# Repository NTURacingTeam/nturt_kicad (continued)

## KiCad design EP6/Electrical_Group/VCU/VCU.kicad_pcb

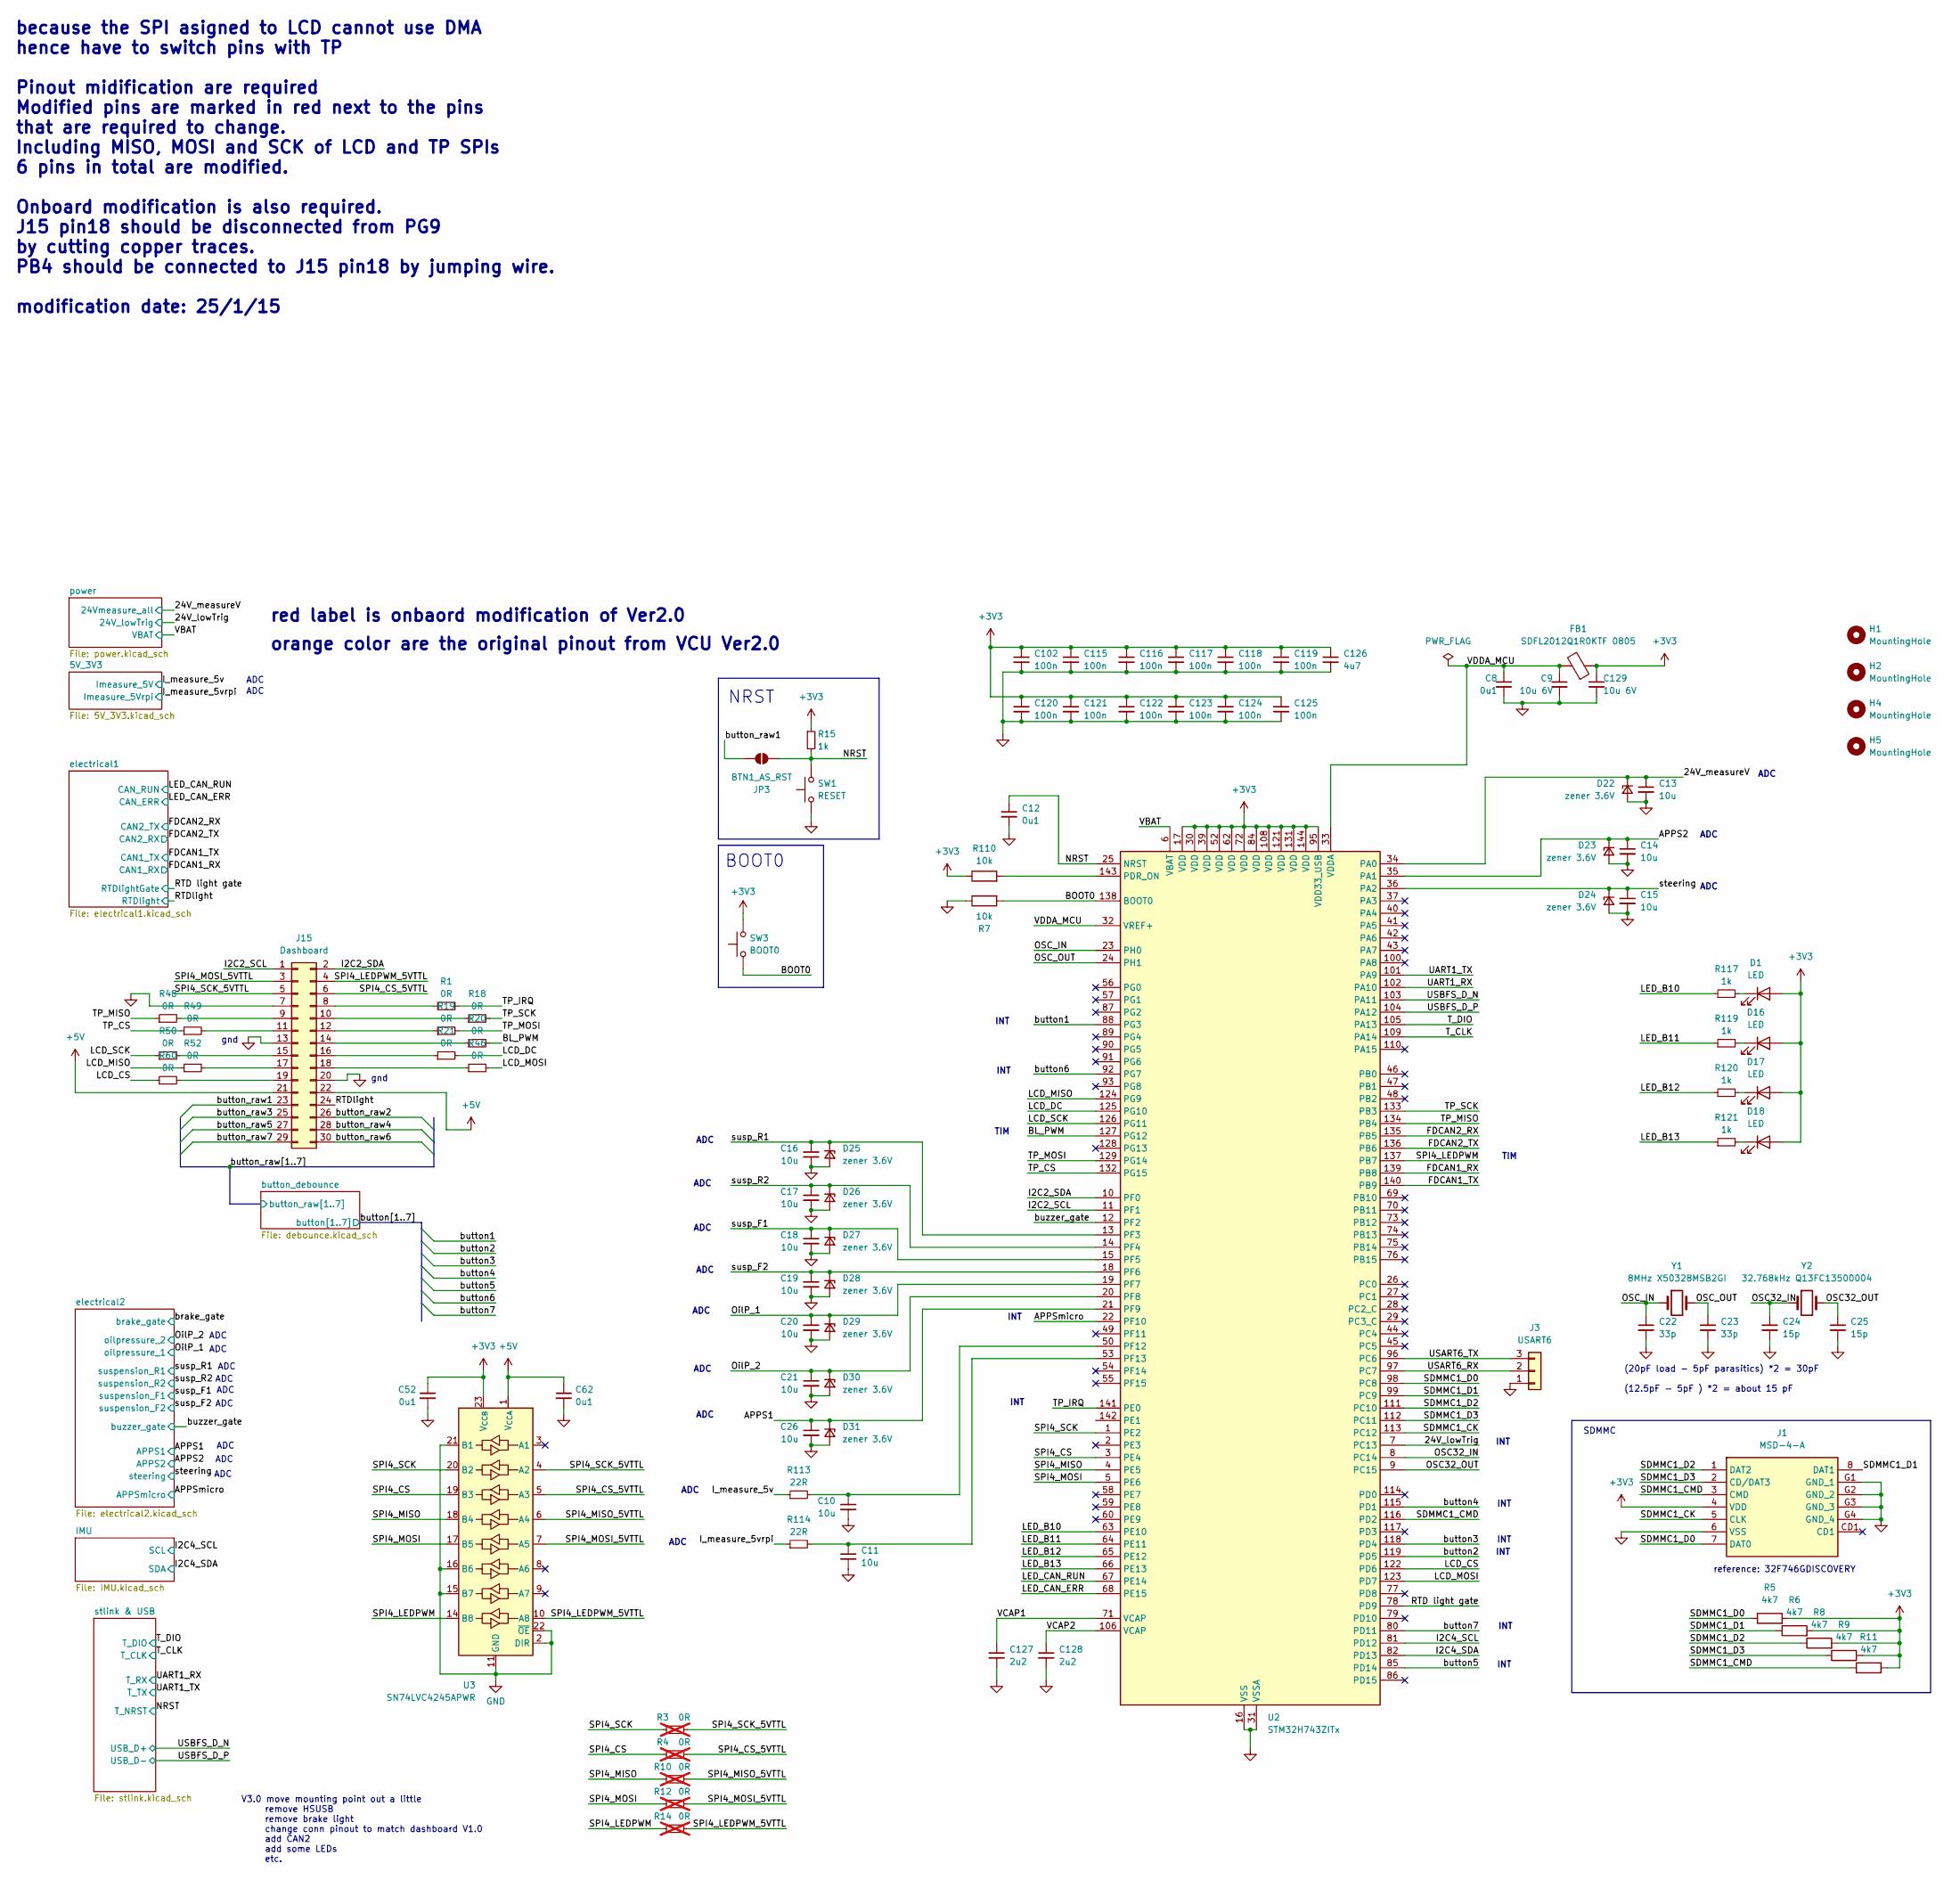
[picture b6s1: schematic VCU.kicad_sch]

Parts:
C8, C12, C52, C62: 0u1; C_0402_1005Metric
C9, C129: 10u 6V; C_0402_1005Metric
C10, C11, C13, C14, C15, C16, C17, C18, C19, C20, C21, C26: 10u; C_0402_1005Metric
C22, C23: 33p; C_0402_1005Metric
C24, C25: 15p; C_0402_1005Metric
C102, C115, C116, C117, C118, C119, C120, C121, C122, C123, C124, C125: 100n; C_0402_1005Metric
C126: 4u7; C_0402_1005Metric
C127, C128: 2u2; C_0402_1005Metric
D1, D16, D17, D18: LED; LED_0603_1608Metric
D22, D23, D24, D25, D26, D27, D28, D29, D30, D31: zener 3.6V; D_SOD-523
FB1: SDFL2012Q1R0KTF 0805; L_0805_2012Metric
H1, H2, H4, H5: MountingHole; MountingHole_3.2mm_M3
J1: MSD-4-A; MSD4A; Mouser Part Number 179-MSD-4-A
J3: USART6; JST_PH_B3B-PH-K_1x03_P2.00mm_Vertical
J15: Dashboard; IDC-Header_2x15_P2.54mm_Vertical
JP3: BTN1_AS_RST; SolderJumper-2_P1.3mm_Open_RoundedPad1.0x1.5mm
R1, R18, R19, R20, R21, R46, R48, R49, R50, R52, R60: 0R; R_0402_1005Metric
R3, R4, R10, R12, R14: 0R; R_0603_1608Metric_Pad0.98x0.95mm_HandSolder; not fitted
R5, R6, R8, R9, R11: 4k7; R_0402_1005Metric
R7, R110: 10k; R_0402_1005Metric
R15, R117, R119, R120, R121: 1k; R_0402_1005Metric
R113, R114: 22R; R_0402_1005Metric
SW1: RESET; SW_Tactile_SPST_NO_Straight_CK_PTS636Sx25SMTRLFS
SW3: BOOT0; SW_Tactile_SPST_NO_Straight_CK_PTS636Sx25SMTRLFS
U2: STM32H743ZITx; LQFP-144_20x20mm_P0.5mm
U3: SN74LVC4245APWR; TSSOP-24_4.4x7.8mm_P0.65mm
Y1: 8MHz X50328MSB2GI; Crystal_SMD_5032-2Pin_5.0x3.2mm
Y2: 32.768kHz Q13FC13500004; Crystal_SMD_3215-2Pin_3.2x1.5mm

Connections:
+3V3: C52.1, C102.1, C115.1, C116.1, C117.1, C118.1, C119.1, C120.1, C121.1, C122.1, C123.1, C124.1, C125.1, C126.1, C129.1, D1.2 (A), D16.2 (A), D17.2 (A), D18.2 (A), FB1.1, J1.4 (VDD), R5.2, R6.2, R8.2, R9.2, R11.2, R15.1, R110.1, SW3.2, U2.17 (VDD), U2.30 (VDD), U2.39 (VDD), U2.52 (VDD), U2.62 (VDD), U2.72 (VDD), U2.84 (VDD), U2.95 (VDD33_USB), U2.108 (VDD), U2.121 (VDD), U2.131 (VDD), U2.144 (VDD), U3.23 (V_{CCB}), U3.24 (V_{CCB}); also elsewhere on the board
+5V: C62.1, J15.21, J15.22, U3.1 (V_{CCA}); also elsewhere on the board
/24V_lowTrig: U2.7 (PC13); also elsewhere on the board
/24V_measureV: C13.1, D22.1 (K), U2.34 (PA0); also elsewhere on the board
/APPS1: C26.1, D31.1 (K), U2.21 (PF9); also elsewhere on the board
/APPS2: C14.1, D23.1 (K), U2.35 (PA1); also elsewhere on the board
/APPSmicro: U2.22 (PF10); also elsewhere on the board
/BL_PWM: R20.2, U2.127 (PG12)
/BOOT0: R7.2, SW3.1, U2.138 (BOOT0)
/FDCAN1_RX: U2.139 (PB8); also elsewhere on the board
/FDCAN1_TX: U2.140 (PB9); also elsewhere on the board
/FDCAN2_RX: U2.135 (PB5); also elsewhere on the board
/FDCAN2_TX: U2.136 (PB6); also elsewhere on the board
/I2C2_SCL: J15.1, U2.11 (PF1)
/I2C2_SDA: J15.2, U2.10 (PF0)
/I2C4_SCL: U2.81 (PD12); also elsewhere on the board
/I2C4_SDA: U2.82 (PD13); also elsewhere on the board
/I_measure_5v: R113.1; also elsewhere on the board
/I_measure_5vrpi: R114.1; also elsewhere on the board
/LCD_CS: R60.1, U2.122 (PD6)
/LCD_DC: R21.2, U2.125 (PG10)
/LCD_MISO: R52.1, U2.124 (PG9)
/LCD_MOSI: R46.2, U2.123 (PD7)
/LCD_SCK: R50.1, U2.126 (PG11)
/LED_B10: R117.1, U2.63 (PE10)
/LED_B11: R119.1, U2.64 (PE11)
/LED_B12: R120.1, U2.65 (PE12)
/LED_B13: R121.1, U2.66 (PE13)
/LED_CAN_ERR: U2.68 (PE15); also elsewhere on the board
/LED_CAN_RUN: U2.67 (PE14); also elsewhere on the board
/NRST: C12.1, JP3.1 (A), R15.2, SW1.2, U2.25 (NRST); also elsewhere on the board
/OSC32_IN: C24.1, U2.8 (PC14), Y2.1
/OSC32_OUT: C25.1, U2.9 (PC15), Y2.2
/OSC_IN: C22.1, U2.23 (PH0), Y1.1
/OSC_OUT: C23.1, U2.24 (PH1), Y1.2
/OilP_1: C20.1, D29.1 (K), U2.19 (PF7); also elsewhere on the board
/OilP_2: C21.1, D30.1 (K), U2.20 (PF8); also elsewhere on the board
/RTD light gate: U2.78 (PD9); also elsewhere on the board
/RTDlight: J15.24; also elsewhere on the board
/SDMMC1_CK: J1.5 (CLK), U2.113 (PC12)
/SDMMC1_CMD: J1.3 (CMD), R11.1, U2.116 (PD2)
/SDMMC1_D0: J1.7 (DAT0), R5.1, U2.98 (PC8)
/SDMMC1_D1: J1.8 (DAT1), R6.1, U2.99 (PC9)
/SDMMC1_D2: J1.1 (DAT2), R8.1, U2.111 (PC10)
/SDMMC1_D3: J1.2 (CD/DAT3), R9.1, U2.112 (PC11)
/SPI4_CS: R4.1, U2.3 (PE4), U3.19 (B3)
/SPI4_CS_5VTTL: J15.6, R4.2, U3.5 (A3)
/SPI4_LEDPWM: R14.1, U2.137 (PB7), U3.14 (B8)
/SPI4_LEDPWM_5VTTL: J15.4, R14.2, U3.10 (A8)
/SPI4_MISO: R10.1, U2.4 (PE5), U3.18 (B4)
/SPI4_MISO_5VTTL: R10.2, U3.6 (A4)
/SPI4_MOSI: R12.1, U2.5 (PE6), U3.17 (B5)
/SPI4_MOSI_5VTTL: J15.3, R12.2, U3.7 (A5)
/SPI4_SCK: R3.1, U2.1 (PE2), U3.20 (B2)
/SPI4_SCK_5VTTL: J15.5, R3.2, U3.4 (A2)
/TP_CS: R49.1, U2.132 (PG15)
/TP_IRQ: R1.1, U2.141 (PE0)
/TP_MISO: R48.1, U2.134 (PB4)
/TP_MOSI: R19.2, U2.129 (PG14)
/TP_SCK: R18.2, U2.133 (PB3)
/T_CLK: U2.109 (PA14); also elsewhere on the board
/T_DIO: U2.105 (PA13); also elsewhere on the board
/UART1_RX: U2.102 (PA10); also elsewhere on the board
/UART1_TX: U2.101 (PA9); also elsewhere on the board
/USART6_RX: J3.2, U2.97 (PC7)
/USART6_TX: J3.3, U2.96 (PC6)
/USBFS_D_N: U2.103 (PA11); also elsewhere on the board
/USBFS_D_P: U2.104 (PA12); also elsewhere on the board
/VBAT: U2.6 (VBAT); also elsewhere on the board
/VCAP1: C127.1, U2.71 (VCAP)
/VCAP2: C128.1, U2.106 (VCAP)
/VDDA_MCU: C8.1, C9.1, FB1.2, U2.32 (VREF+), U2.33 (VDDA)
/button1: U2.88 (PG3); also elsewhere on the board
/button2: U2.119 (PD5); also elsewhere on the board
/button3: U2.118 (PD4); also elsewhere on the board
/button4: U2.115 (PD1); also elsewhere on the board
/button5: U2.85 (PD14); also elsewhere on the board
/button6: U2.92 (PG7); also elsewhere on the board
/button7: U2.80 (PD11); also elsewhere on the board
/button_raw1: J15.23, JP3.2 (B); also elsewhere on the board
/button_raw2: J15.26; also elsewhere on the board
/button_raw3: J15.25; also elsewhere on the board
/button_raw4: J15.28; also elsewhere on the board
/button_raw5: J15.27; also elsewhere on the board
/button_raw6: J15.30; also elsewhere on the board
/button_raw7: J15.29; also elsewhere on the board
/buzzer_gate: U2.12 (PF2); also elsewhere on the board
/steering: C15.1, D24.1 (K), U2.36 (PA2); also elsewhere on the board
/susp_F1: C18.1, D27.1 (K), U2.15 (PF5); also elsewhere on the board
/susp_F2: C19.1, D28.1 (K), U2.18 (PF6); also elsewhere on the board
/susp_R1: C16.1, D25.1 (K), U2.13 (PF3); also elsewhere on the board
/susp_R2: C17.1, D26.1 (K), U2.14 (PF4); also elsewhere on the board
GND: C8.2, C9.2, C10.2, C11.2, C12.2, C13.2, C14.2, C15.2, C16.2, C17.2, C18.2, C19.2, C20.2, C21.2, C22.2, C23.2, C24.2, C25.2, C26.2, C52.2, C62.2, C102.2, C115.2, C116.2, C117.2, C118.2, C119.2, C120.2, C121.2, C122.2, C123.2, C124.2, C125.2, C126.2, C127.2, C128.2, C129.2, D22.2 (A), D23.2 (A), D24.2 (A), D25.2 (A), D26.2 (A), D27.2 (A), D28.2 (A), D29.2 (A), D30.2 (A), D31.2 (A), J1.6 (VSS), J1.G1 (GND_1), J1.G2 (GND_2), J1.G3 (GND_3), J1.G4 (GND_4), J3.1, J15.7, J15.13, J15.20, R7.1, SW1.1, U2.16 (VSS), U2.31 (VSSA), U2.38 (VSS), U2.51 (VSS), U2.61 (VSS), U2.83 (VSS), U2.94 (VSS), U2.107 (VSS), U2.120 (VSS), U2.130 (VSS), U3.2 (DIR), U3.11 (GND), U3.12 (GND), U3.13 (GND), U3.15 (B7), U3.16 (B6), U3.21 (B1), U3.22 (~OE); also elsewhere on the board
unnamed: D1.1 (K), R117.2
unnamed: D16.1 (K), R119.2
unnamed: D17.1 (K), R120.2
unnamed: D18.1 (K), R121.2
unnamed: J15.8, R1.2
unnamed: J15.9, R48.2
unnamed: J15.10, R18.1
unnamed: J15.11, R49.2
unnamed: J15.12, R19.1
unnamed: J15.14, R20.1
unnamed: J15.15, R50.2
unnamed: J15.16, R21.1
unnamed: J15.17, R52.2
unnamed: J15.18, R46.1
unnamed: J15.19, R60.2
unnamed: R110.2, U2.143 (PDR_ON)
unnamed: C10.1, R113.2, U2.50 (PF12)
unnamed: C11.1, R114.2, U2.53 (PF13)

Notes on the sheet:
INT
ADC
BOOT0
NRST
gnd
orange color are the original pinout from VCU Ver2.0
V3.0 move mounting point out a little remove HSUSB remove brake light change conn pinout to match dashboard V1.0 add CAN2 add some LEDs etc.
TIM
SDMMC
reference: 32F746GDISCOVERY
(20pF load - 5pF parasitics) *2 = 30pF (12.5pF - 5pF ) *2 = about 15 pF
red label is onbaord modification of Ver2.0
because the SPI asigned to LCD cannot use DMA hence have to switch pins with TP Pinout midification are required Modified pins are marked in red next to the pins that are required to change. Including MISO, MOSI and SCK of LCD and TP SPIs 6 pins in total are modified. Onboard modification is also r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

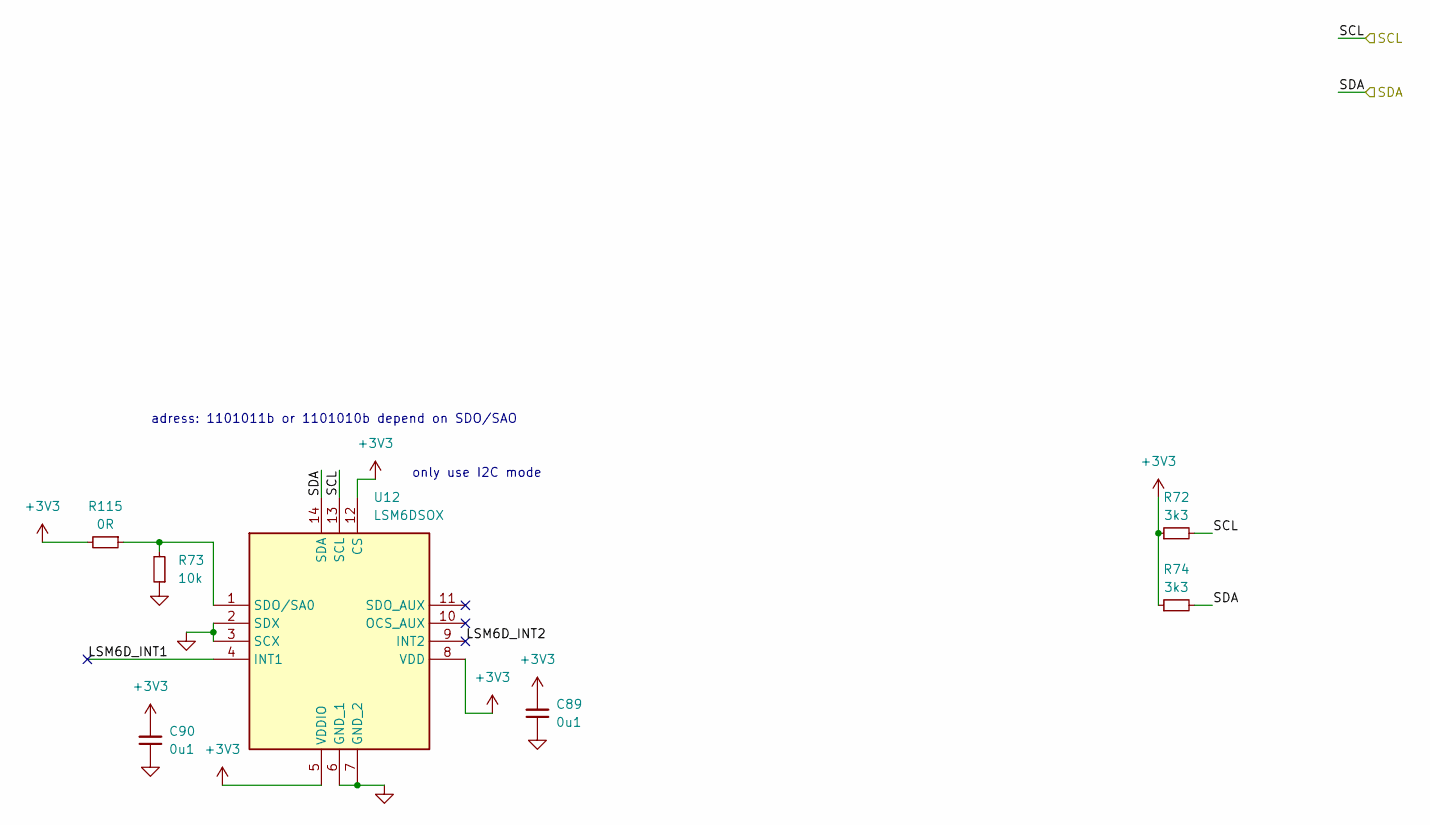
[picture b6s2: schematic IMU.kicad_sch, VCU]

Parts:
C89, C90: 0u1; C_0402_1005Metric
R72, R74: 3k3; R_0402_1005Metric
R73: 10k; R_0402_1005Metric
R115: 0R; R_0402_1005Metric
U12: LSM6DSOX; LGA-14_3x2.5mm_P0.5mm_LayoutBorder3x4y; Mouser Part Number 511-LSM6DSOXTR

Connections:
+3V3: C89.2, C90.2, R72.1, R74.1, R115.2, U12.5 (VDDIO), U12.8 (VDD), U12.12 (CS); also elsewhere on the board
/I2C4_SCL: R72.2, U12.13 (SCL); also elsewhere on the board
/I2C4_SDA: R74.2, U12.14 (SDA); also elsewhere on the board
/IMU/LSM6D_INT1: U12.4 (INT1)
/IMU/LSM6D_INT2: U12.9 (INT2)
GND: C89.1, C90.1, R73.1, U12.2 (SDX), U12.3 (SCX), U12.6 (GND_1), U12.7 (GND_2); also elsewhere on the board
unnamed: R73.2, R115.1, U12.1 (SDO/SA0)

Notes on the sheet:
adress: 1101011b or 1101010b depend on SDO/SAO
only use I2C mode

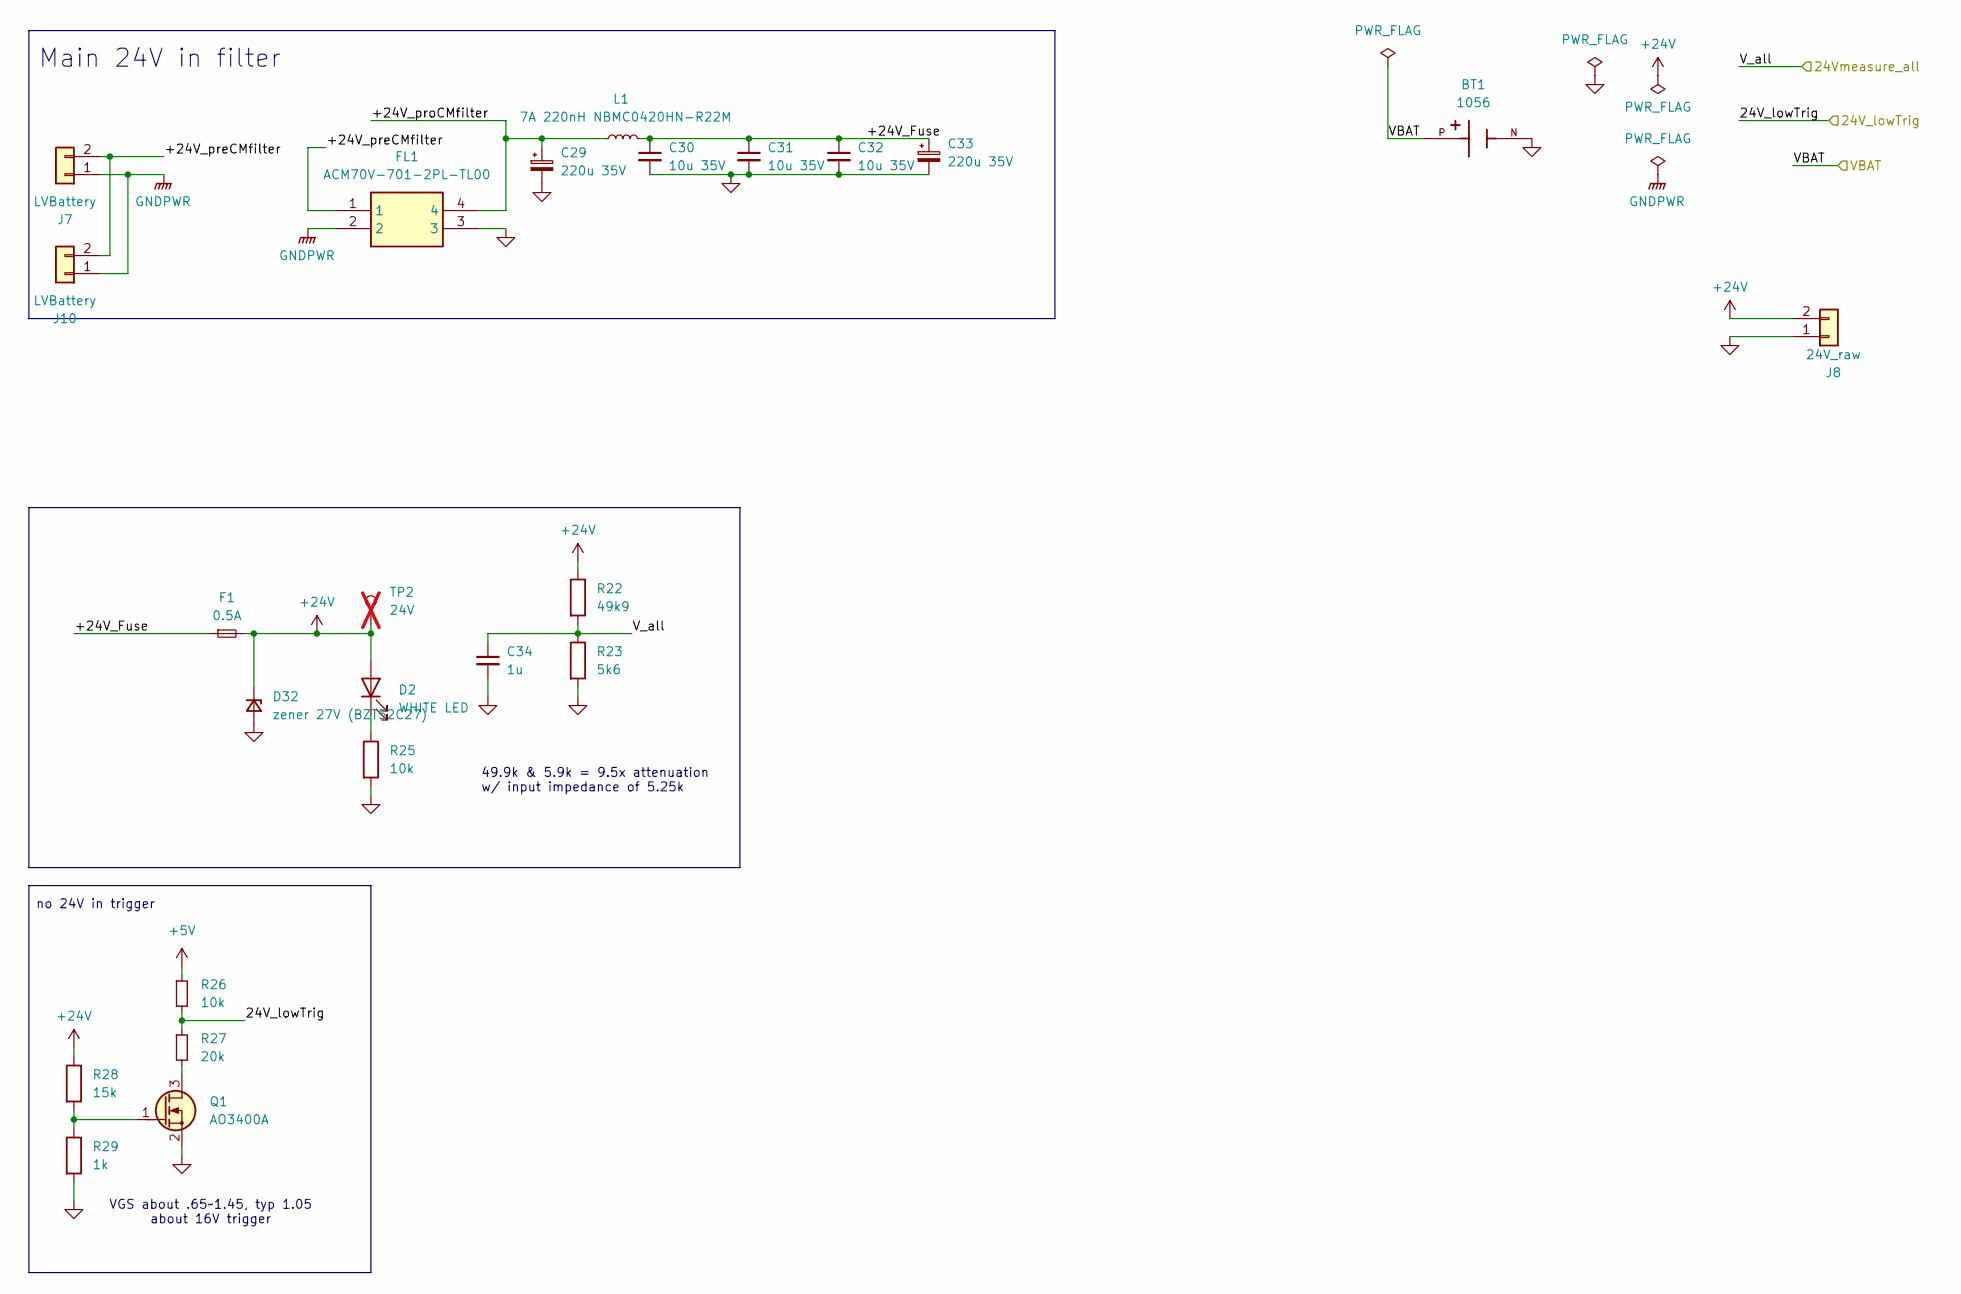
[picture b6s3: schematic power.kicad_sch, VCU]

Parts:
BT1: 1056; BAT_1056; PARTREV D
C29, C33: 220u 35V; CP_Radial_D8.0mm_P3.80mm
C30, C31, C32: 10u 35V; C_1206_3216Metric
C34: 1u; C_0402_1005Metric
D2: WHITE LED; LED_0603_1608Metric
D32: zener 27V (BZT52C27); D_SOD-123
F1: 0.5A; Fuse_1206_3216Metric
FL1: ACM70V-701-2PL-TL00; ACM70V7012PLTL00; Mouser Part Number 810-ACM70V7012PLTL00
J7, J10: LVBattery; JST_XH_B2B-XH-A_1x02_P2.50mm_Vertical
J8: 24V_raw; JST_XH_B2B-XH-A_1x02_P2.50mm_Vertical
L1: 7A 220nH NBMC0420HN-R22M; L_Ferrocore_DLG-0403
Q1: AO3400A; SOT-23
R22: 49k9; R_0402_1005Metric
R23: 5k6; R_0402_1005Metric
R25, R26: 10k; R_0402_1005Metric
R27: 20k; R_0402_1005Metric
R28: 15k; R_0402_1005Metric
R29: 1k; R_0402_1005Metric
TP2: 24V; TestPoint_Pad_D1.0mm; not fitted

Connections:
+5V: R26.1; also elsewhere on the board
+24V: D2.2 (A), D32.1 (K), F1.2, J8.2, R22.1, R28.1, TP2.1; also elsewhere on the board
/24V_lowTrig: R26.2, R27.1; also elsewhere on the board
/24V_measureV: C34.1, R22.2, R23.1; also elsewhere on the board
/VBAT: BT1.P; also elsewhere on the board
/power/+24V_Fuse: C30.1, C31.1, C32.1, C33.1, F1.1, L1.2
/power/+24V_preCMfilter: FL1.1, J7.2, J10.2
/power/+24V_proCMfilter: C29.1, FL1.4, L1.1
GND: BT1.N, C29.2, C30.2, C31.2, C32.2, C33.2, C34.2, D32.2 (A), FL1.3, J8.1, Q1.2 (S), R23.2, R25.2, R29.2; also elsewhere on the board
GNDPWR: FL1.2, J7.1, J10.1
unnamed: D2.1 (K), R25.1
unnamed: Q1.3 (D), R27.2
unnamed: Q1.1 (G), R28.2, R29.1

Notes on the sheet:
no 24V in trigger
49.9k & 5.9k = 9.5x attenuation w/ input impedance of 5.25k
Main 24V in filter
VGS about .65~1.45, typ 1.05 about 16V trigger

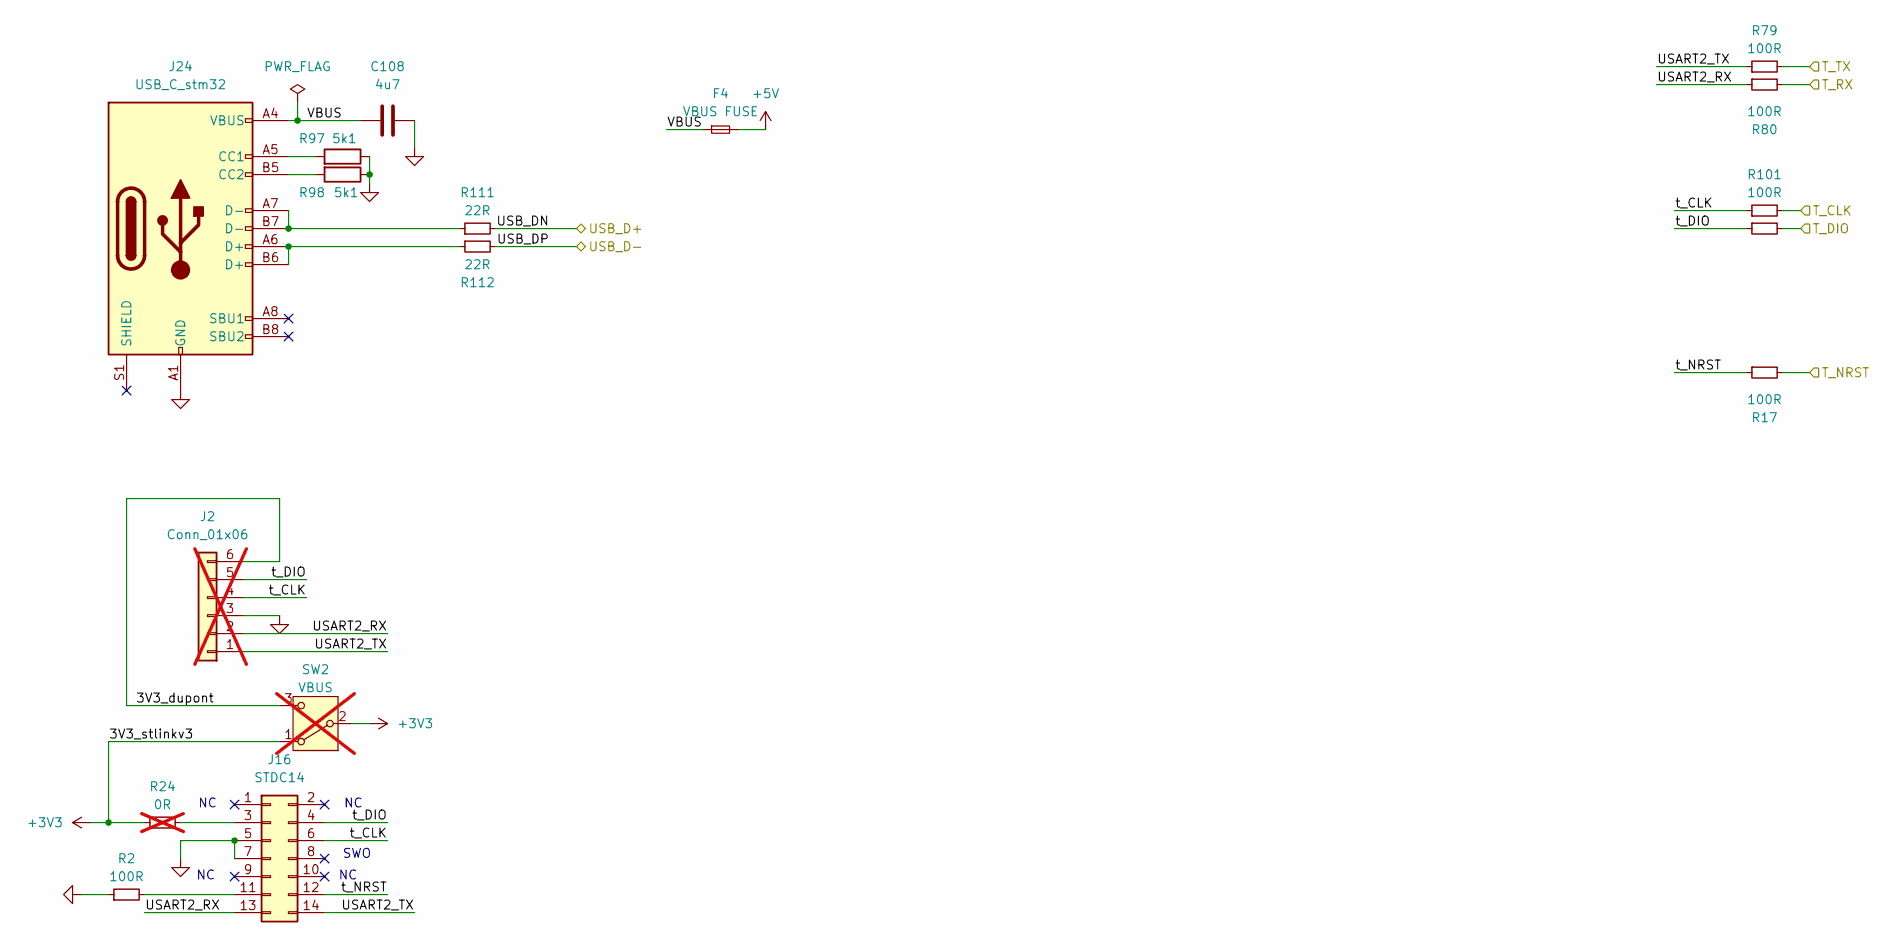
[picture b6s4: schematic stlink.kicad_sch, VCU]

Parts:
C108: 4u7; C_0402_1005Metric
F4: VBUS FUSE; Fuse_1206_3216Metric
J2: Conn_01x06; PinHeader_1x06_P2.54mm_Horizontal; not fitted
J16: STDC14; box_header_14P_pitch127
J24: USB_C_stm32; USB_C_Receptacle_GCT_USB4105-xx-A_16P_TopMnt_Horizontal
R2, R17, R79, R80, R101, R105: 100R; R_0402_1005Metric
R24: 0R; R_0402_1005Metric; not fitted
R97, R98: 5k1; R_0402_1005Metric
R111, R112: 22R; R_0402_1005Metric
SW2: VBUS; PinHeader_1x03_P2.54mm_Vertical; not fitted

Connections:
+3V3: R24.1, SW2.1 (A), SW2.2 (B); also elsewhere on the board
+5V: F4.2; also elsewhere on the board
/NRST: R17.2; also elsewhere on the board
/T_CLK: R101.2; also elsewhere on the board
/T_DIO: R105.2; also elsewhere on the board
/UART1_RX: R80.2; also elsewhere on the board
/UART1_TX: R79.2; also elsewhere on the board
/USBFS_D_N: R111.2; also elsewhere on the board
/USBFS_D_P: R112.2; also elsewhere on the board
/stlink & USB/USART2_RX: J2.2, J16.13, R80.1
/stlink & USB/USART2_TX: J2.1, J16.14, R79.1
/stlink & USB/VBUS: C108.1, F4.1, J24.A4 (VBUS), J24.A9 (VBUS), J24.B4 (VBUS), J24.B9 (VBUS)
/stlink & USB/t_CLK: J2.4, J16.6, R101.1
/stlink & USB/t_DIO: J2.5, J16.4, R105.1
/stlink & USB/t_NRST: J16.12, R17.1
GND: C108.2, J2.3, J16.5, J16.7, J24.A1 (GND), J24.A12 (GND), J24.B1 (GND), J24.B12 (GND), R2.1, R97.1, R98.1; also elsewhere on the board
unnamed: J2.6, SW2.3 (C)
unnamed: J16.3, R24.2
unnamed: J16.11, R2.2
unnamed: J24.A5 (CC1), R97.2
unnamed: J24.B5 (CC2), R98.2
unnamed: J24.A6 (D+), J24.B6 (D+), R112.1
unnamed: J24.A7 (D-), J24.B7 (D-), R111.1

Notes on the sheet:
SWO

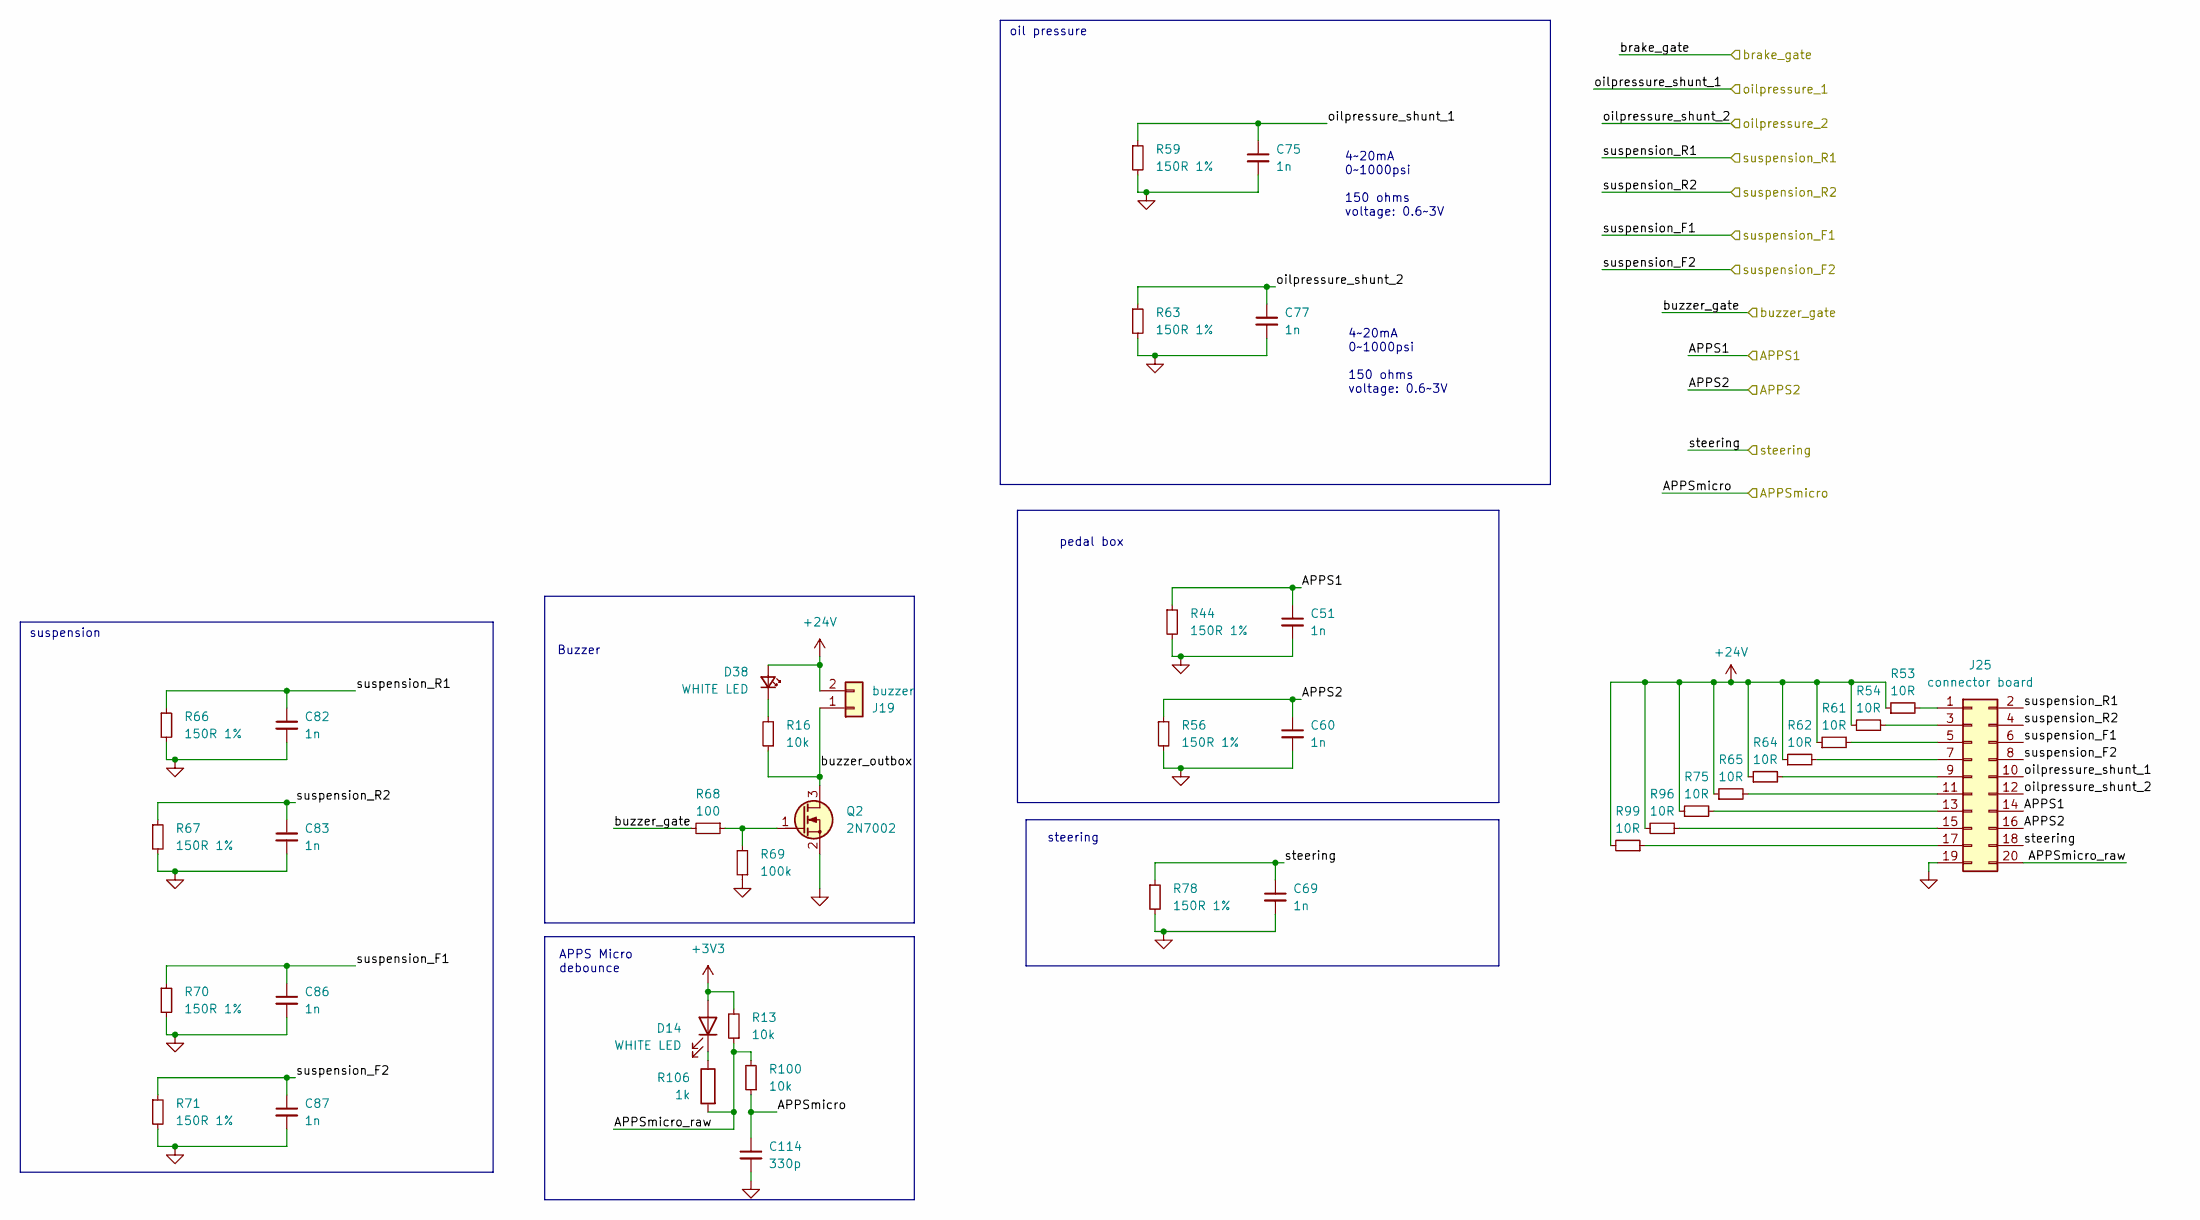
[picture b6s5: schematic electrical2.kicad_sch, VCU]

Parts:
C51, C60, C69, C75, C77, C82, C83, C86, C87: 1n; C_0402_1005Metric
C114: 330p; C_0402_1005Metric
D14, D38: WHITE LED; LED_0603_1608Metric
J19: buzzer; JST_XH_B2B-XH-A_1x02_P2.50mm_Vertical
J25: connector board; IDC-Header_2x10_P2.54mm_Vertical
Q2: 2N7002; SOT-23
R13, R16, R100: 10k; R_0402_1005Metric
R44, R56, R59, R63, R66, R67, R70, R71, R78: 150R 1%; R_0603_1608Metric
R53, R54, R61, R62, R64, R65, R75, R96, R99: 10R; R_0603_1608Metric
R68: 100; R_0402_1005Metric
R69: 100k; R_0402_1005Metric
R106: 1k; R_0402_1005Metric

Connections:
+3V3: D14.2 (A), R13.2; also elsewhere on the board
+24V: D38.2 (A), J19.2, R53.1, R54.1, R61.1, R62.1, R64.1, R65.1, R75.1, R96.2, R99.2; also elsewhere on the board
/APPS1: C51.1, J25.14, R44.1; also elsewhere on the board
/APPS2: C60.1, J25.16, R56.1; also elsewhere on the board
/APPSmicro: C114.1, R100.1; also elsewhere on the board
/OilP_1: C75.1, J25.10, R59.1; also elsewhere on the board
/OilP_2: C77.1, J25.12, R63.1; also elsewhere on the board
/buzzer_gate: R68.2; also elsewhere on the board
/electrical2/APPSmicro_raw: J25.20, R13.1, R100.2, R106.2
/electrical2/buzzer_outbox: J19.1, Q2.3 (D), R16.1
/steering: C69.1, J25.18, R78.1; also elsewhere on the board
/susp_F1: C86.1, J25.6, R70.1; also elsewhere on the board
/susp_F2: C87.1, J25.8, R71.1; also elsewhere on the board
/susp_R1: C82.1, J25.2, R66.1; also elsewhere on the board
/susp_R2: C83.1, J25.4, R67.1; also elsewhere on the board
GND: C51.2, C60.2, C69.2, C75.2, C77.2, C82.2, C83.2, C86.2, C87.2, C114.2, J25.19, Q2.2 (S), R44.2, R56.2, R59.2, R63.2, R66.2, R67.2, R69.1, R70.2, R71.2, R78.2; also elsewhere on the board
unnamed: D14.1 (K), R106.1
unnamed: D38.1 (K), R16.2
unnamed: J25.1, R53.2
unnamed: J25.3, R54.2
unnamed: J25.5, R61.2
unnamed: J25.7, R62.2
unnamed: J25.9, R64.2
unnamed: J25.11, R65.2
unnamed: J25.13, R75.2
unnamed: J25.15, R96.1
unnamed: J25.17, R99.1
unnamed: Q2.1 (G), R68.1, R69.2

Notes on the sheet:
steering
pedal box
4~20mA 0~1000psi 150 ohms voltage: 0.6~3V
Buzzer
suspension
oil pressure
APPS Micro debounce
